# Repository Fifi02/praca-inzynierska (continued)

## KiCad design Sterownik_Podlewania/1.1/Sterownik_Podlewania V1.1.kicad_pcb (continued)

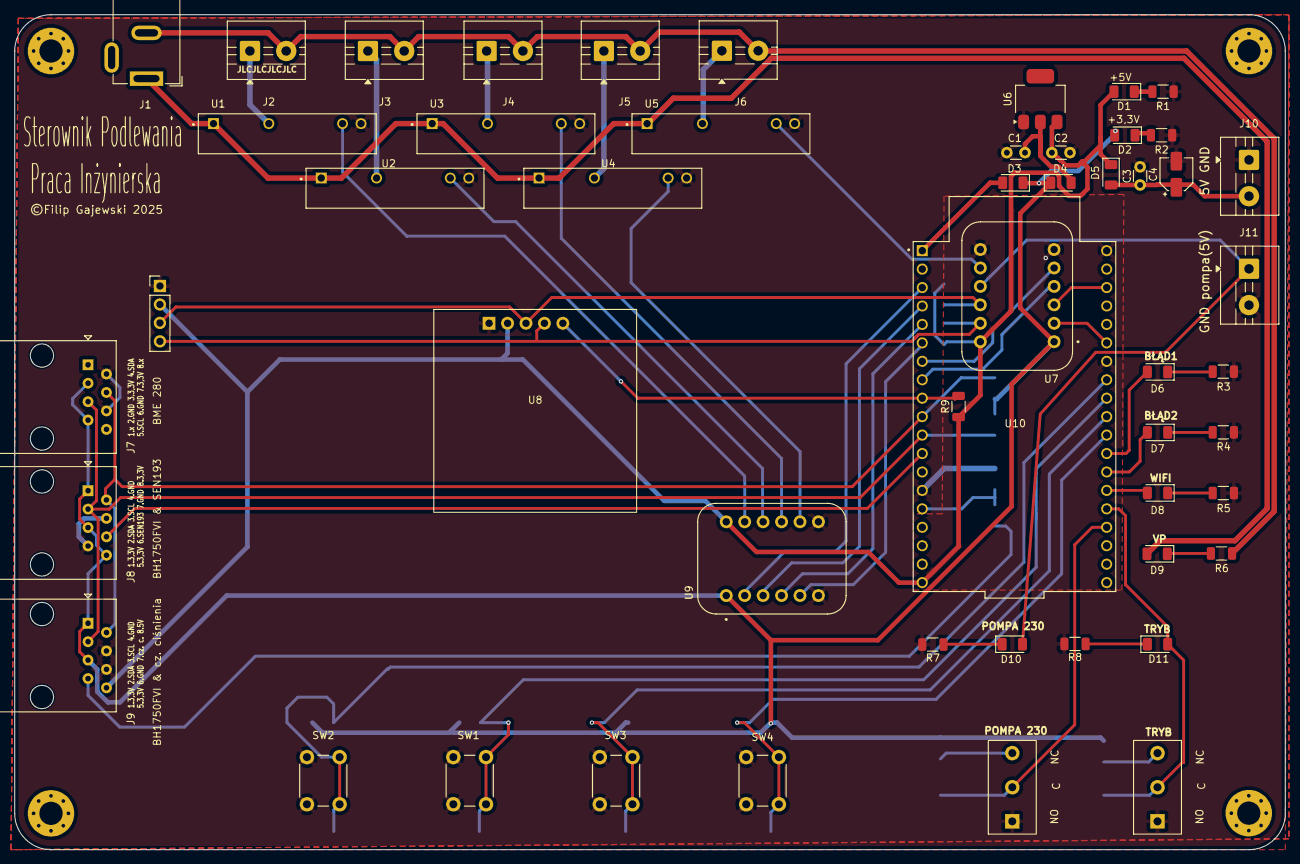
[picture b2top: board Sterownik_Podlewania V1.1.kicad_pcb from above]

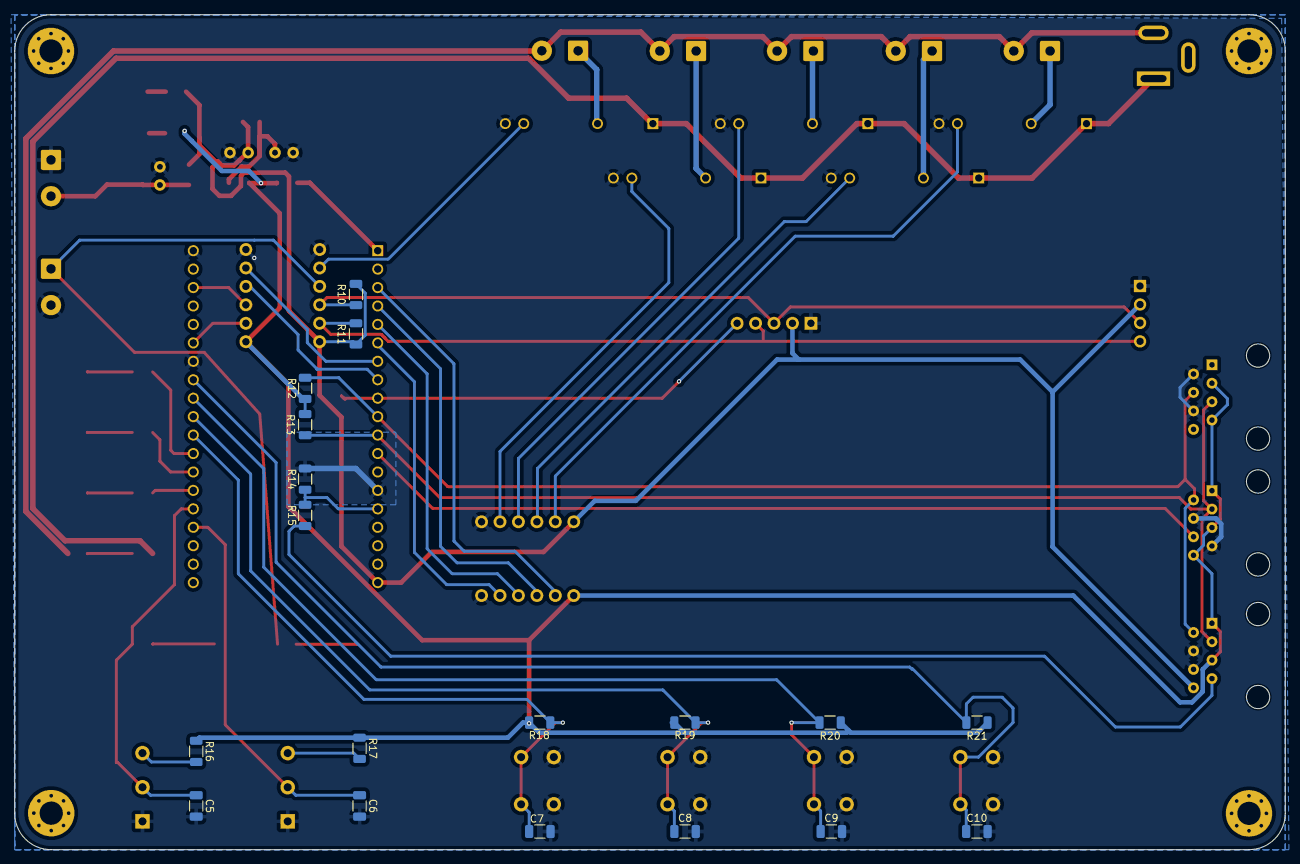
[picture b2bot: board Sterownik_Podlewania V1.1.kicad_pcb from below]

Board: 2 copper layers, 175.0 x 115.0 mm, 70 parts (18 on the bottom side), 54 nets.

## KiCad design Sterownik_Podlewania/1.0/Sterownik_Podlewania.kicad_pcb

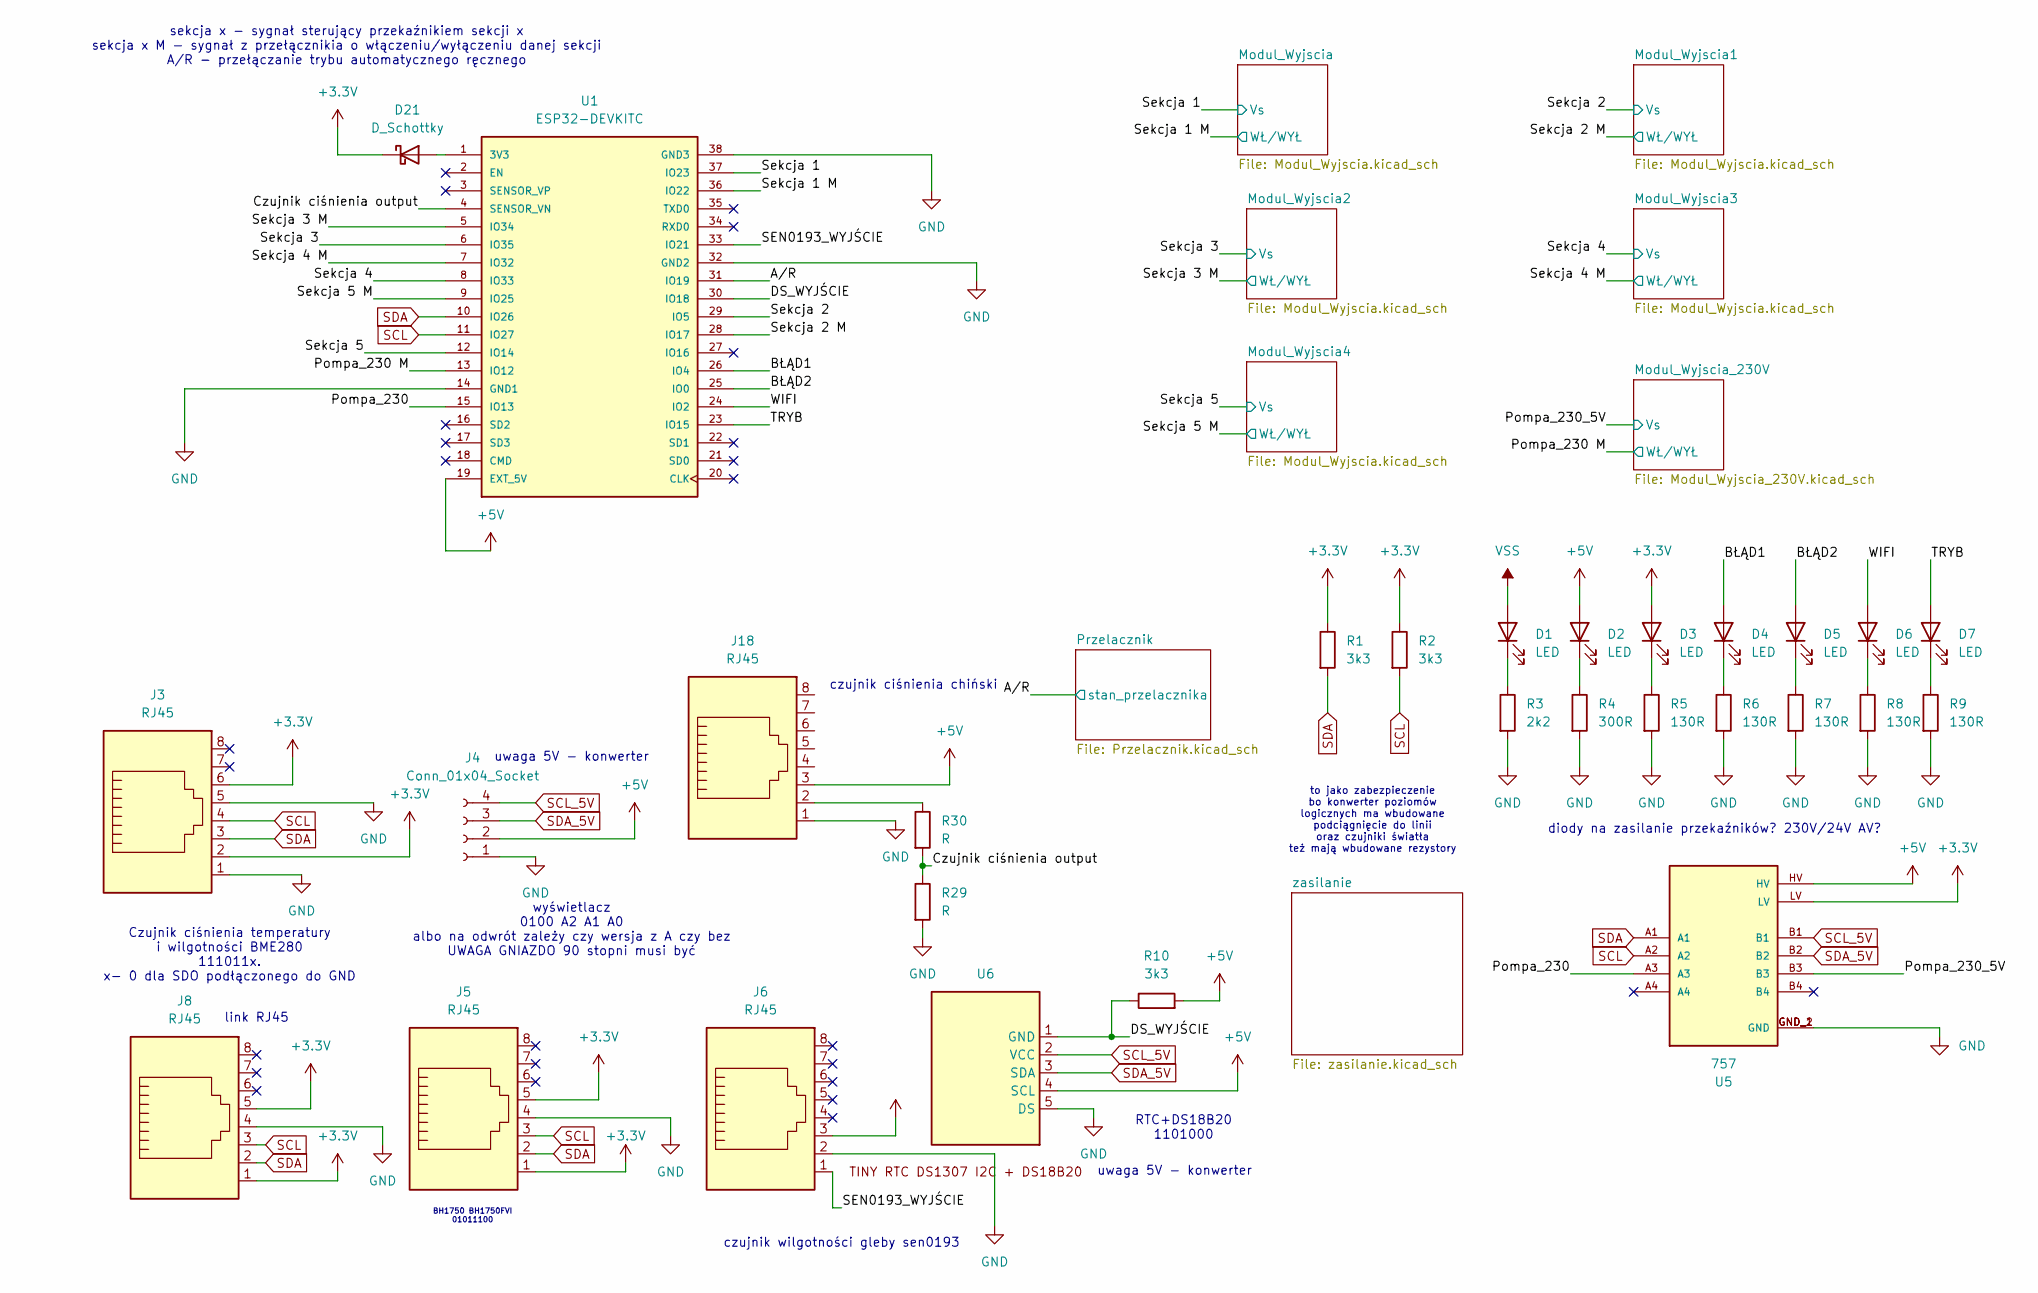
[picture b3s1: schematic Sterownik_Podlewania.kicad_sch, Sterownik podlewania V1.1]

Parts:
D1, D2, D3, D4, D5, D6, D7: LED; LED_1206_3216Metric
D21: D_Schottky; D_1206_3216Metric
J3, J5, J6, J8, J18: RJ45; RJ45_Amphenol_54602-x08_Horizontal
J4: Conn_01x04_Socket; PinHeader_1x04_P2.54mm_Vertical
R1, R2, R10: 3k3; R_1206_3216Metric
R3: 2k2; R_1206_3216Metric
R4: 300R; R_1206_3216Metric
R5, R6, R7, R8, R9: 130R; R_1206_3216Metric
R29, R30: R; R_1206_3216Metric
U1: ESP32-DEVKITC; MODULE_ESP32-DEVKITC; PARTREV N/A
U5: 757; MODULE_757; PARTREV N/A
U6: RTC DS1307 + 32kb EEPROM 24C32 I2C

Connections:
+3.3V: D3.2 (A), D21.1 (K), J3.2, J3.6, J5.1, J5.5, J6.3, J8.1, J8.5, R1.1, R2.1, U5.LV; also elsewhere on the board
+5V: D2.2 (A), J4.2, J18.3, R10.2, U1.19 (EXT_5V), U5.HV, U6.4 (SCL); also elsewhere on the board
/A/R: U1.31 (IO19); also elsewhere on the board
/BŁĄD1: D4.2 (A), U1.26 (IO4)
/BŁĄD2: D5.2 (A), U1.25 (IO0)
/Czujnik ciśnienia output: R29.1, R30.2, U1.4 (SENSOR_VN)
/DS_WYJŚCIE: R10.1, U1.30 (IO18), U6.1 (GND)
/Pompa_230: U1.15 (IO13), U5.A3
/Pompa_230 M: U1.13 (IO12); also elsewhere on the board
/Pompa_230_5V: U5.B3; also elsewhere on the board
/SEN0193_WYJŚCIE: J6.1, U1.33 (IO21)
/Sekcja 1: U1.37 (IO23); also elsewhere on the board
/Sekcja 1 M: U1.36 (IO22); also elsewhere on the board
/Sekcja 2: U1.29 (IO5); also elsewhere on the board
/Sekcja 2 M: U1.28 (IO17); also elsewhere on the board
/Sekcja 3: U1.6 (IO35); also elsewhere on the board
/Sekcja 3 M: U1.5 (IO34); also elsewhere on the board
/Sekcja 4: U1.8 (IO33); also elsewhere on the board
/Sekcja 4 M: U1.7 (IO32); also elsewhere on the board
/Sekcja 5: U1.12 (IO14); also elsewhere on the board
/Sekcja 5 M: U1.9 (IO25); also elsewhere on the board
/TRYB: D7.2 (A), U1.23 (IO15)
/WIFI: D6.2 (A), U1.24 (IO2)
GND: J3.1, J3.5, J4.1, J5.4, J6.2, J8.4, J18.1, R3.2, R4.2, R5.2, R6.2, R7.2, R8.2, R9.2, R29.2, U1.14 (GND1), U1.32 (GND2), U1.38 (GND3), U5.GND_1 (GND), U5.GND_2 (GND), U6.5 (DS); also elsewhere on the board
unnamed: D1.1 (K), R3.1
unnamed: D2.1 (K), R4.1
unnamed: D3.1 (K), R5.1
unnamed: D4.1 (K), R6.1
unnamed: D5.1 (K), R7.1
unnamed: D6.1 (K), R8.1
unnamed: D7.1 (K), R9.1
unnamed: D21.2 (A), U1.1 (3V3)
unnamed: J18.2, R30.1
SCL: J3.4, J5.3, J8.3, R2.2, U1.11 (IO27), U5.A2
SCL_5V: J4.4, U5.B1, U6.2 (VCC)
SDA: J3.3, J5.2, J8.2, R1.2, U1.10 (IO26), U5.A1
SDA_5V: J4.3, U5.B2, U6.3 (SDA)
VSS: D1.2 (A); also elsewhere on the board

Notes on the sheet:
uwaga 5V - konwerter
sekcja x - sygnał sterujący przekaźnikiem sekcji x sekcja x M - sygnał z przełącznikia o włączeniu/wyłączeniu danej sekcji A/R - przełączanie trybu automatycznego ręcznego
czujnik wilgotności gleby sen0193
diody na zasilanie przekaźników? 230V/24V AV?
to jako zabezpieczenie bo konwerter poziomów logicznych ma wbudowane podciągnięcie do linii oraz czujniki światła też mają wbudowane rezystory
BH1750 BH1750FVI 01011100
link RJ45
wyświetlacz 0100 A2 A1 A0 albo na odwrót zależy czy wersja z A czy bez UWAGA GNIAZDO 90 stopni musi być
Czujnik ciśnienia temperatury i wilgotności BME280 111011x. x- 0 dla SDO podłączonego do GND
czujnik ciśnienia chiński
RTC+DS18B20 1101000

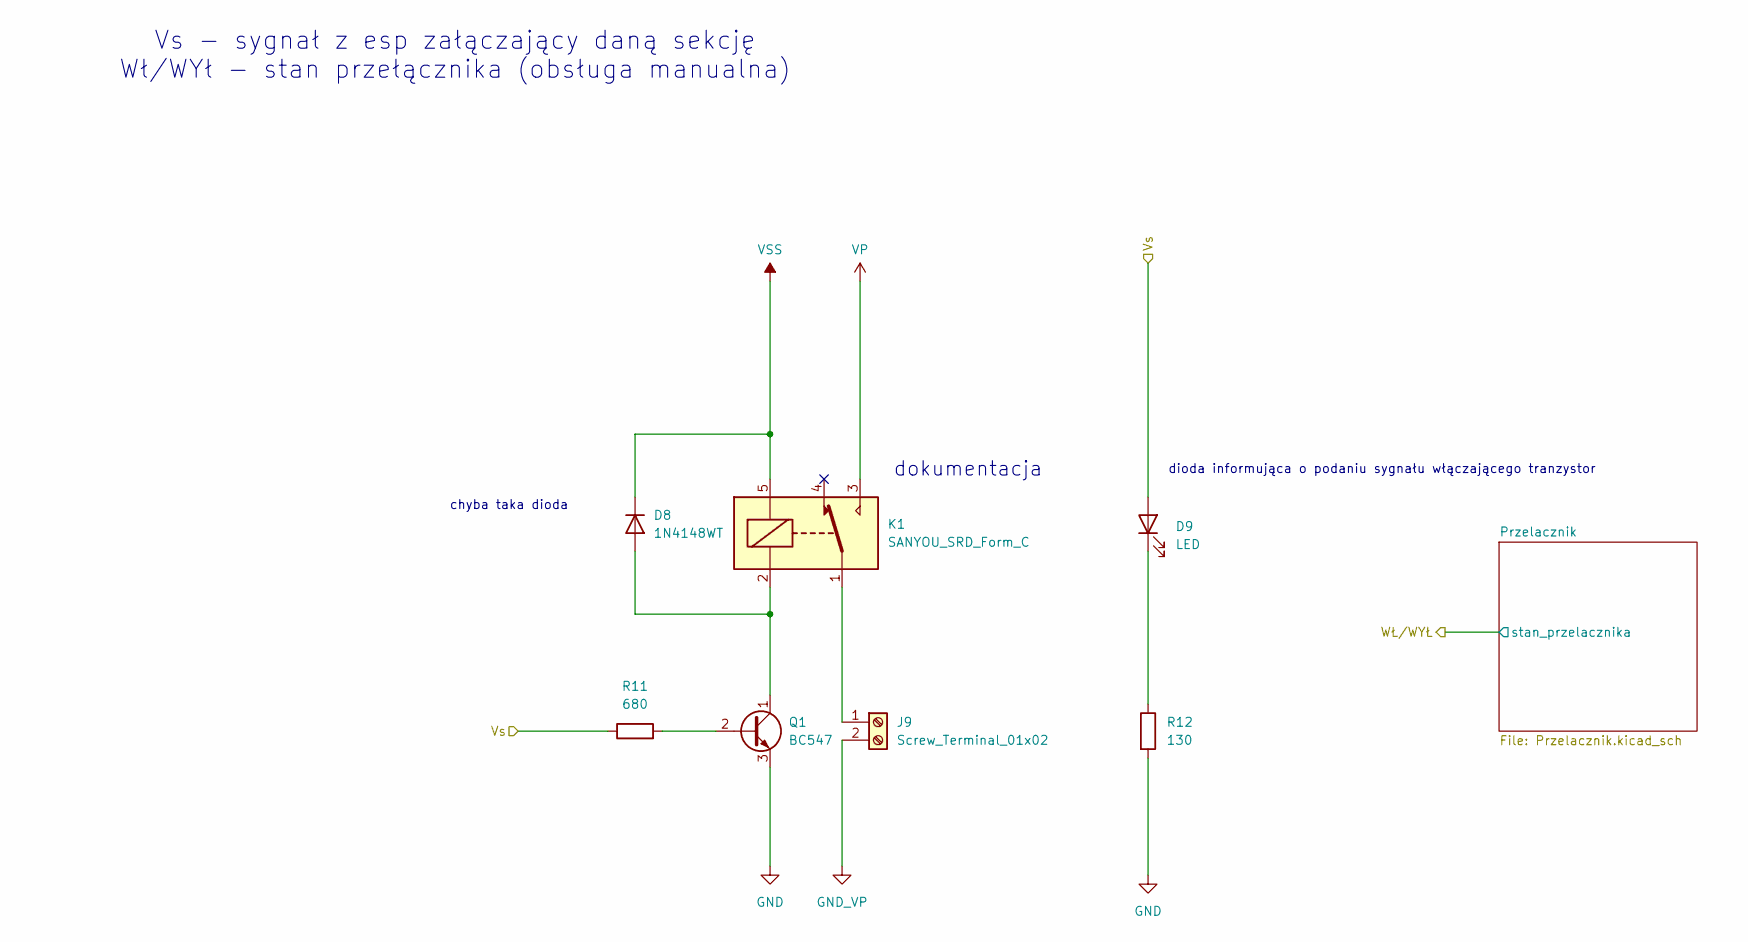
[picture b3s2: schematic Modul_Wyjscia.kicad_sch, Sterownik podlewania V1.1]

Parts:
D8: 1N4148WT; D_1206_3216Metric
D9: LED; LED_1206_3216Metric
J9: Screw_Terminal_01x02; TerminalBlock_MaiXu_MX126-5.0-02P_1x02_P5.00mm
K1: SANYOU_SRD_Form_C; Relay_SPDT_SANYOU_SRD_Series_Form_C
Q1: BC547; TO-92_Inline
R11: 680; R_1206_3216Metric
R12: 130; R_1206_3216Metric

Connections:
/Sekcja 1: D9.2 (A), R11.1; also elsewhere on the board
GND: Q1.3 (E), R12.2; also elsewhere on the board
GND_VP: J9.2; also elsewhere on the board
unnamed: D8.2 (A), K1.2, Q1.1 (C)
unnamed: D9.1 (K), R12.1
unnamed: J9.1, K1.1
unnamed: Q1.2 (B), R11.2
VP: K1.3; also elsewhere on the board
VSS: D8.1 (K), K1.5; also elsewhere on the board

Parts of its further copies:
D10, D12, D14, D16: 1N4148WT; D_1206_3216Metric
D11, D13, D15, D17: LED; LED_1206_3216Metric
J10, J11, J12, J13: Screw_Terminal_01x02; TerminalBlock_MaiXu_MX126-5.0-02P_1x02_P5.00mm
K2, K3, K4, K5: SANYOU_SRD_Form_C; Relay_SPDT_SANYOU_SRD_Series_Form_C
Q2, Q3, Q4, Q5: BC547; TO-92_Inline
R13, R15, R17, R19: 680; R_1206_3216Metric
R14, R16, R18, R20: 130; R_1206_3216Metric

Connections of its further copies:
/Sekcja 2: D11.2 (A), R13.1; also elsewhere on the board
/Sekcja 3: D13.2 (A), R15.1; also elsewhere on the board
/Sekcja 4: D15.2 (A), R17.1; also elsewhere on the board
/Sekcja 5: D17.2 (A), R19.1; also elsewhere on the board
GND: Q2.3 (E), Q3.3 (E), Q4.3 (E), Q5.3 (E), R14.2, R16.2, R18.2, R20.2; also elsewhere on the board
GND_VP: J10.2, J11.2, J12.2, J13.2; also elsewhere on the board
unnamed: D10.2 (A), K2.2, Q2.1 (C)
unnamed: D11.1 (K), R14.1
unnamed: D12.2 (A), K3.2, Q3.1 (C)
unnamed: D13.1 (K), R16.1
unnamed: D14.2 (A), K4.2, Q4.1 (C)
unnamed: D15.1 (K), R18.1
unnamed: D16.2 (A), K5.2, Q5.1 (C)
unnamed: D17.1 (K), R20.1
unnamed: J10.1, K2.1
unnamed: J11.1, K3.1
unnamed: J12.1, K4.1
unnamed: J13.1, K5.1
unnamed: Q2.2 (B), R13.2
unnamed: Q3.2 (B), R15.2
unnamed: Q4.2 (B), R17.2
unnamed: Q5.2 (B), R19.2
VP: K2.3, K3.3, K4.3, K5.3; also elsewhere on the board
VSS: D10.1 (K), D12.1 (K), D14.1 (K), D16.1 (K), K2.5, K3.5, K4.5, K5.5; also elsewhere on the board

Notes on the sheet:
Vs - sygnał z esp załączający daną sekcję Wł/WYł - stan przełącznika (obsługa manualna)
dioda informująca o podaniu sygnału włączającego tranzystor
chyba taka dioda
dokumentacja

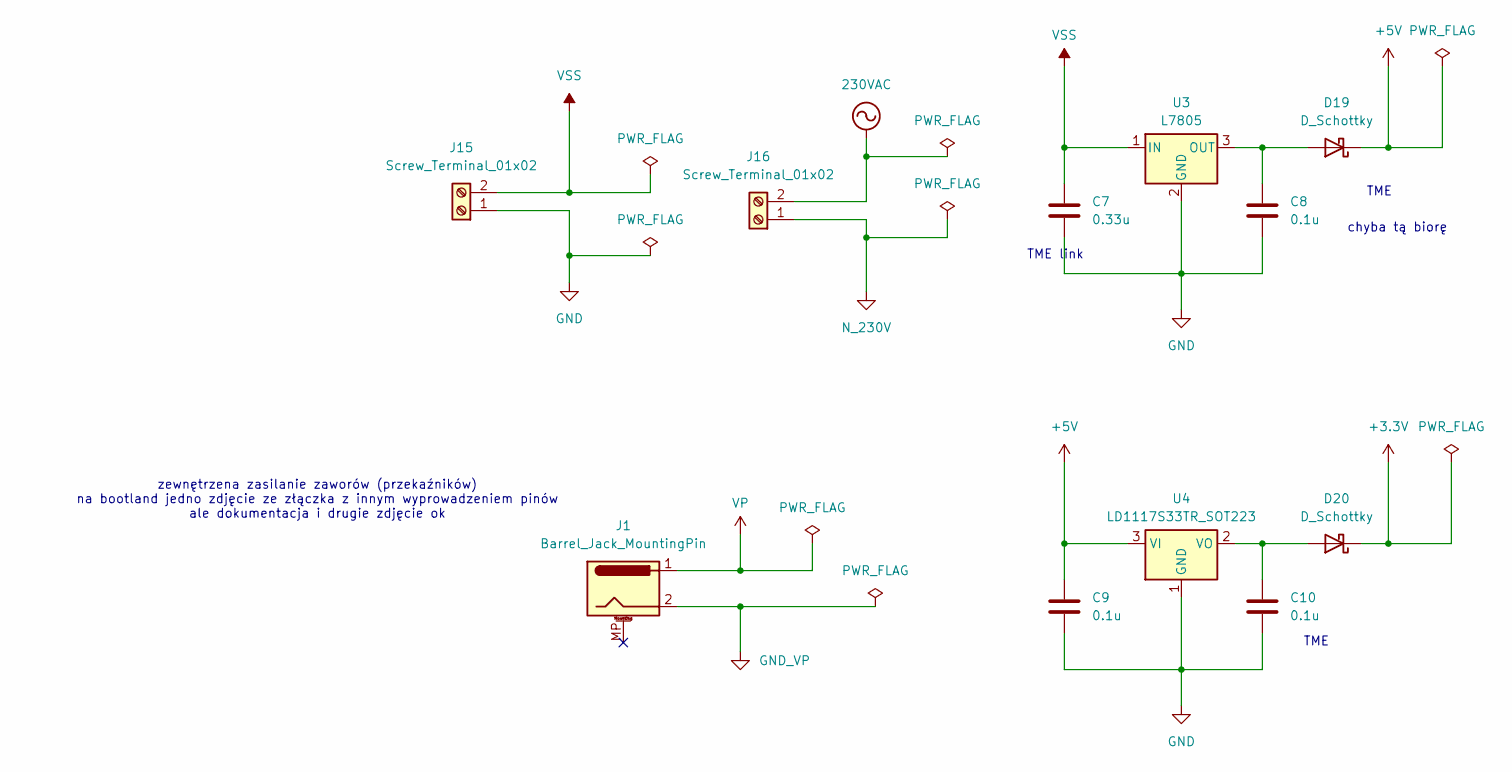
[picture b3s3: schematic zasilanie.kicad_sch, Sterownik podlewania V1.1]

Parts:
C7: 0.33u; CP_Elec_4x5.4
C8, C9, C10: 0.1u; C_Disc_D3.0mm_W1.6mm_P2.50mm
D19, D20: D_Schottky; D_1206_3216Metric
J1: Barrel_Jack_MountingPin; BarrelJack_GCT_DCJ200-10-A_Horizontal
J15, J16: Screw_Terminal_01x02; TerminalBlock_MaiXu_MX126-5.0-02P_1x02_P5.00mm
U3: L7805; TO-220-3_Vertical
U4: LD1117S33TR_SOT223; SOT-223

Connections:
230VAC: J16.2; also elsewhere on the board
+3.3V: D20.1 (K); also elsewhere on the board
+5V: C9.1, D19.1 (K), U4.3 (VI); also elsewhere on the board
GND: C7.2, C8.2, C9.2, C10.2, J15.1, U3.2 (GND), U4.1 (GND); also elsewhere on the board
GND_VP: J1.2; also elsewhere on the board
N_230V: J16.1; also elsewhere on the board
unnamed: C8.1, D19.2 (A), U3.3 (OUT)
unnamed: C10.1, D20.2 (A), U4.2 (VO)
VP: J1.1; also elsewhere on the board
VSS: C7.1, J15.2, U3.1 (IN); also elsewhere on the board

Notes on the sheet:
TME link
TME
chyba tą biorę
zewnętrzena zasilanie zaworów (przekaźników) na bootland jedno zdjęcie ze złączka z innym wyprowadzeniem pinów ale dokumentacja i drugie zdjęcie ok

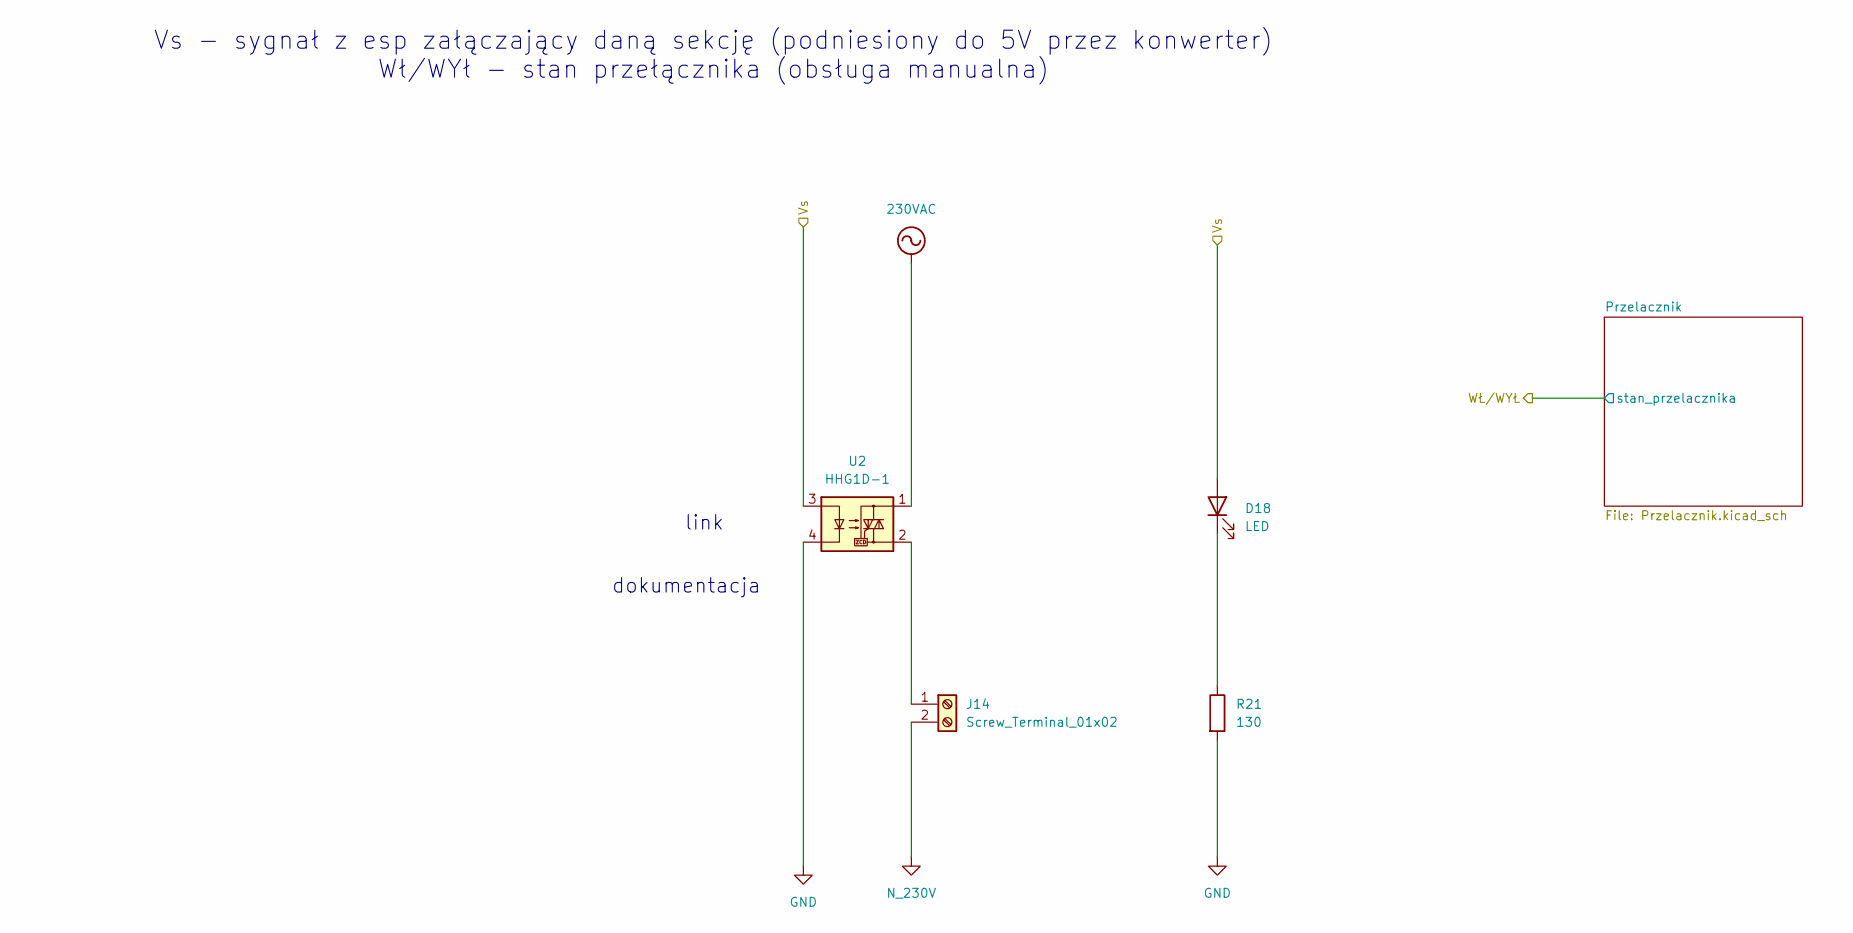
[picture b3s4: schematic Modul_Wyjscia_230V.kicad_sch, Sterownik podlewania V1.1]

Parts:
D18: LED; LED_1206_3216Metric
J14: Screw_Terminal_01x02; TerminalBlock_MaiXu_MX126-5.0-02P_1x02_P5.00mm
R21: 130; R_1206_3216Metric
U2: HHG1D-1; RELAY_G3MB-202P

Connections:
230VAC: U2.1; also elsewhere on the board
/Pompa_230_5V: D18.2 (A), U2.3; also elsewhere on the board
GND: R21.2, U2.4; also elsewhere on the board
N_230V: J14.2; also elsewhere on the board
unnamed: D18.1 (K), R21.1
unnamed: J14.1, U2.2

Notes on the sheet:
Vs - sygnał z esp załączający daną sekcję (podniesiony do 5V przez konwerter) Wł/WYł - stan przełącznika (obsługa manualna)
dokumentacja
link

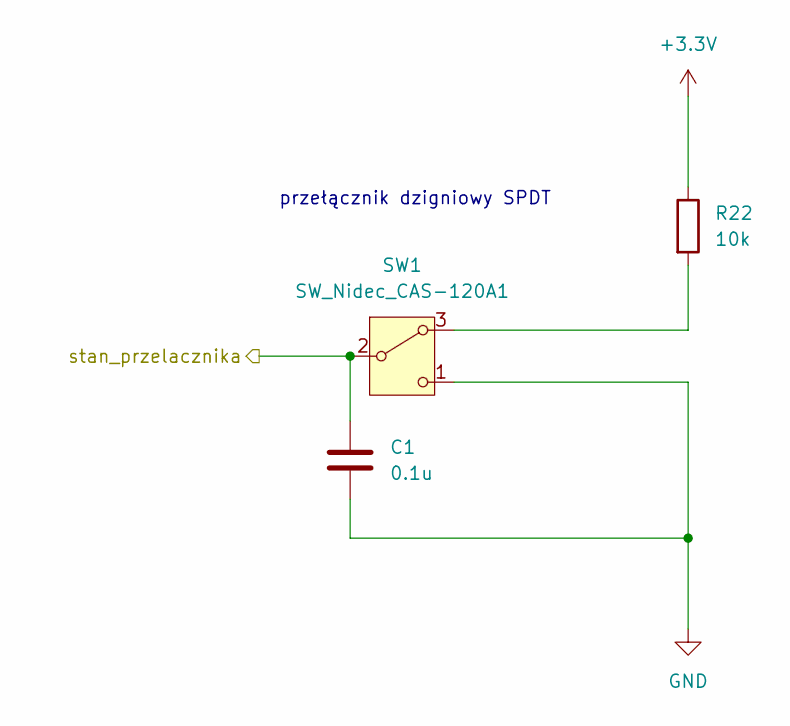
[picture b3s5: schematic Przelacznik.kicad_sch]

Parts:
C1: 0.1u; C_1206_3216Metric
R22: 10k; R_1206_3216Metric
SW1: SW_Nidec_CAS-120A1; Toggle Switch Bootland 4.7mm

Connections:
+3.3V: R22.1; also elsewhere on the board
/A/R: C1.1, SW1.2 (B); also elsewhere on the board
GND: C1.2, SW1.1 (C); also elsewhere on the board
unnamed: R22.2, SW1.3 (A)

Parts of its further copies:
C2, C3, C4, C5, C6, C11: 0.1u; C_1206_3216Metric
R23, R24, R25, R26, R27, R28: 10k; R_1206_3216Metric
SW2, SW3, SW4, SW5, SW6, SW8: SW_Nidec_CAS-120A1; Toggle Switch Bootland 4.7mm

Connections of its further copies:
+3.3V: R23.1, R24.1, R25.1, R26.1, R27.1, R28.1; also elsewhere on the board
/Pompa_230 M: C11.1, SW8.2 (B); also elsewhere on the board
/Sekcja 1 M: C2.1, SW2.2 (B); also elsewhere on the board
/Sekcja 2 M: C3.1, SW3.2 (B); also elsewhere on the board
/Sekcja 3 M: C4.1, SW4.2 (B); also elsewhere on the board
/Sekcja 4 M: C5.1, SW5.2 (B); also elsewhere on the board
/Sekcja 5 M: C6.1, SW6.2 (B); also elsewhere on the board
GND: C2.2, C3.2, C4.2, C5.2, C6.2, C11.2, SW2.1 (C), SW3.1 (C), SW4.1 (C), SW5.1 (C), SW6.1 (C), SW8.1 (C); also elsewhere on the board
unnamed: R23.2, SW2.3 (A)
unnamed: R24.2, SW3.3 (A)
unnamed: R25.2, SW4.3 (A)
unnamed: R26.2, SW5.3 (A)
unnamed: R27.2, SW6.3 (A)
unnamed: R28.2, SW8.3 (A)

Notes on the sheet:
przełącznik dzigniowy SPDT

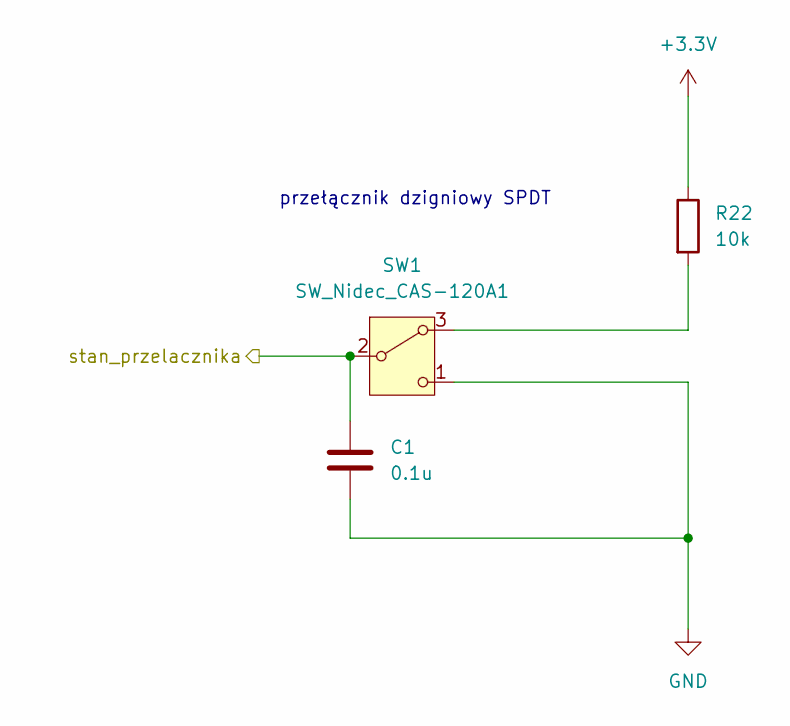
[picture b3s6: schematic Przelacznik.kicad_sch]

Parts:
C1: 0.1u; C_1206_3216Metric
R22: 10k; R_1206_3216Metric
SW1: SW_Nidec_CAS-120A1; Nidec_Copal_CAS-120A

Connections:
+3.3V: R22.1; also elsewhere on the board
/A/R: C1.1, SW1.2 (B); also elsewhere on the board
GND: C1.2, SW1.1 (C); also elsewhere on the board
unnamed: R22.2, SW1.3 (A)

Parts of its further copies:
C2, C3, C4, C5, C6, C11: 0.1u; C_1206_3216Metric
R23, R24, R25, R26, R27, R28: 10k; R_1206_3216Metric
SW2, SW3, SW4, SW5, SW6, SW8: SW_Nidec_CAS-120A1; Nidec_Copal_CAS-120A

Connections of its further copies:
+3.3V: R23.1, R24.1, R25.1, R26.1, R27.1, R28.1; also elsewhere on the board
/Pompa_230 M: C11.1, SW8.2 (B); also elsewhere on the board
/Sekcja 1 M: C2.1, SW2.2 (B); also elsewhere on the board
/Sekcja 2 M: C3.1, SW3.2 (B); also elsewhere on the board
/Sekcja 3 M: C4.1, SW4.2 (B); also elsewhere on the board
/Sekcja 4 M: C5.1, SW5.2 (B); also elsewhere on the board
/Sekcja 5 M: C6.1, SW6.2 (B); also elsewhere on the board
GND: C2.2, C3.2, C4.2, C5.2, C6.2, C11.2, SW2.1 (C), SW3.1 (C), SW4.1 (C), SW5.1 (C), SW6.1 (C), SW8.1 (C); also elsewhere on the board
unnamed: R23.2, SW2.3 (A)
unnamed: R24.2, SW3.3 (A)
unnamed: R25.2, SW4.3 (A)
unnamed: R26.2, SW5.3 (A)
unnamed: R27.2, SW6.3 (A)
unnamed: R28.2, SW8.3 (A)

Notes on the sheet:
przełącznik dzigniowy SPDT

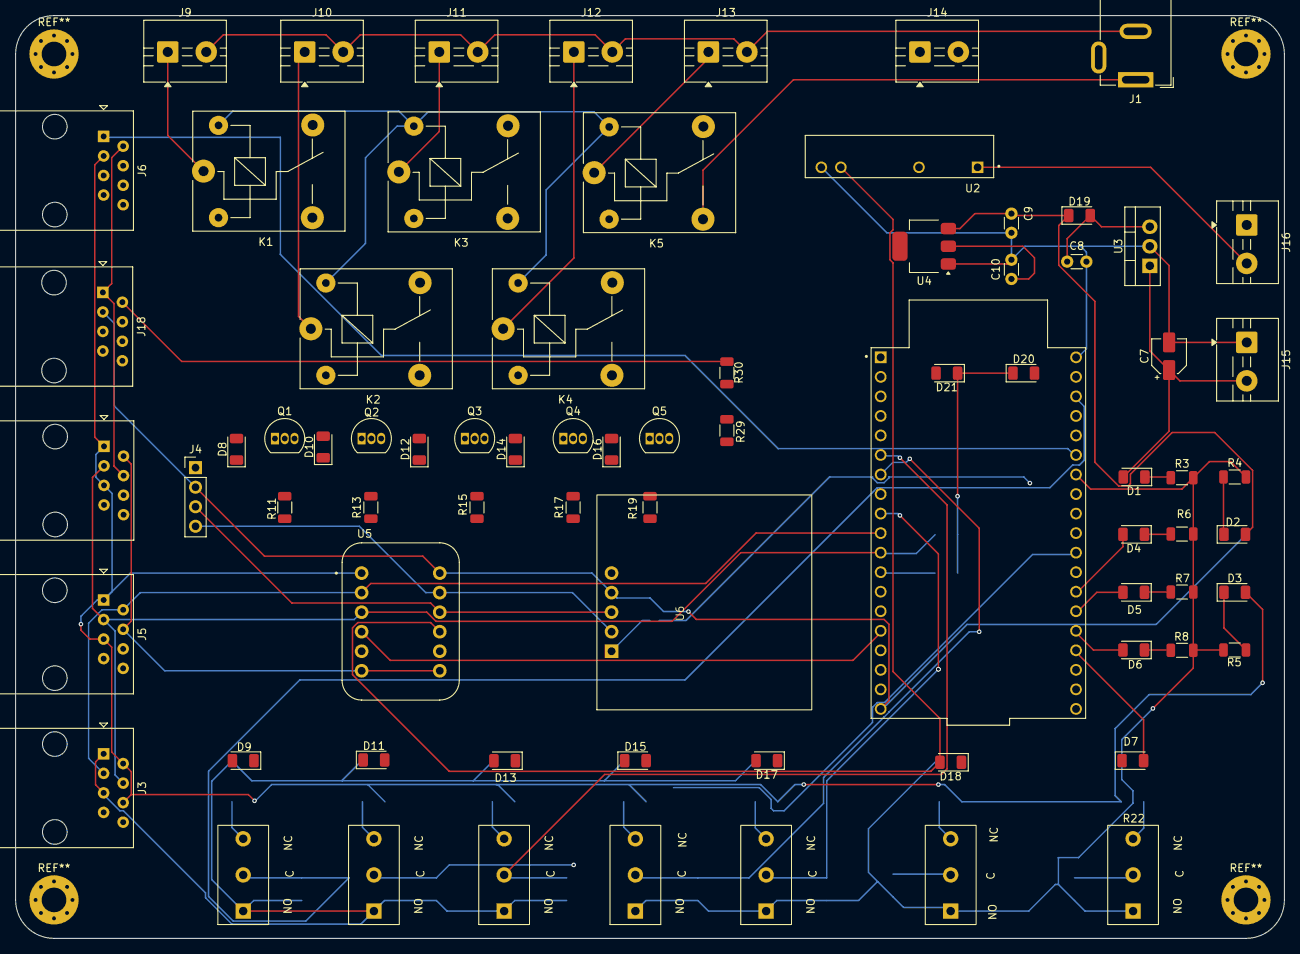
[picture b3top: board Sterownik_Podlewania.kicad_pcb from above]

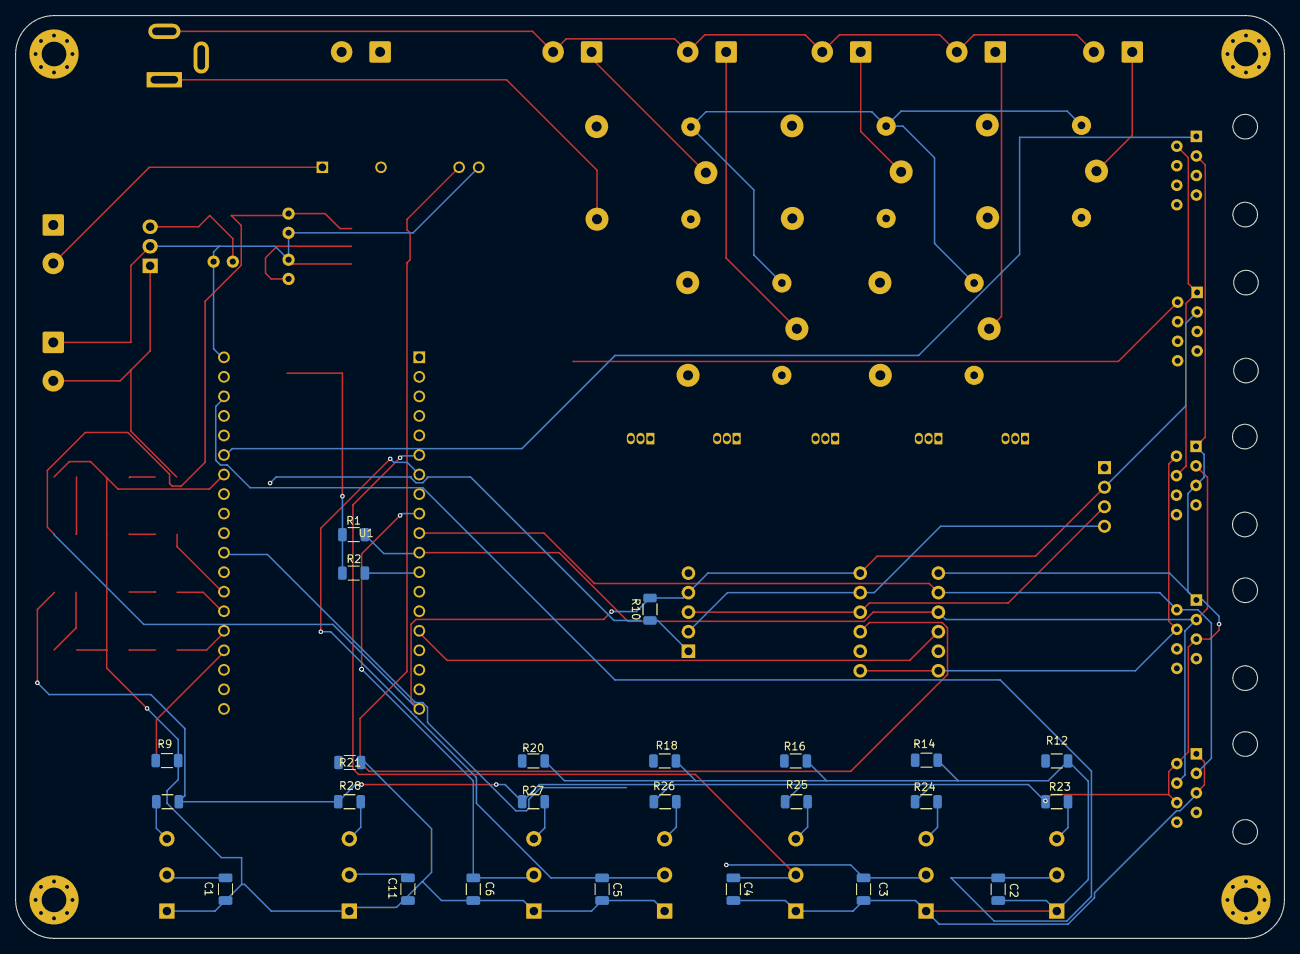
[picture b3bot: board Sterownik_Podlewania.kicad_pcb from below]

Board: 2 copper layers, 165.0 x 120.0 mm, 100 parts (24 on the bottom side), 73 nets.

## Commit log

2025-09-17 Pierwsze koty za płoty
2025-09-18 Dodanie zasilania, sekcji czujników światła, modyfikacja przełączników, dodanie znaczników
2025-10-04 Modyfikacja sekcji czujników
2025-10-04 Dodanie adresów I2C, linków, czujnika temp, konwerter poziomów napięć
2025-10-05 Dodanie większośi footprinów, dodanie osobno sekcji na 230V, dodanie jacka DC
2025-10-07 Dodanie dokumentacji przełączników, sprawdzenie konwertera I2C, dodanie sekcji przełącznika, dodanie DIP swticha do przełączania zasialania zew, wydzielenie sekcji zasilania
2025-10-08 Poprawki estetyczne schematu
2025-10-09 Dodanie gniazd ethernet, poprawienie większośc ERC
2025-10-09 Wstępny układ PCB
2025-10-10 Dodanie footprintów schotky, kondesatorów
2025-10-12 Dodanie modeli 3d, nowy footprint do przełącznika, przerzucenie na drugą stronę płytki elementów, wstępne rozdzielenie elemntów pasywnych
2025-10-14 dodanie modeli 3d, poprawa footprintu RTC
2025-10-15 Wstępny finalny rozkład płytki, narysowanie outlinu
2025-10-16 Zmiana footprintó diód przekaźnika na schottky,finalne ułożenie przekaźników, diód itp
2025-10-18 Wersja 1.1 rozkład footprintów, dopracowanie schematu V1.1
2025-10-18 Pociągnięcie prawie wszystkich ścieżek, dodanie rezystorów do I2C 5V
2025-10-19 Poprawiono błędy połączeń SDA,SCL, dodno drugą magistralę I2C, pociągnięcie nowych ścieżek
2025-10-23 Dodanie modułu zasilania, wstępny schemat
2025-10-24 Poprawki schematu modułu zaworu, usunięcie przekaźnika, przygotowanie schematu zasilania
2025-10-24 Usunięcie zewnętrzego zasilania 12 i stabilizatora napięcia, korekcja zasilania wzmacniacz operacyjny moduł zasilania
2025-10-25 Poprawki moduł zasilania, stowrzenie płytki, zostało trochę błędów, zapomniałem dać mouting holes
2025-10-26 Gotowy do zatwierdzenia moduł zasilaina
2025-10-26 Werja plików podesłana Mariuszkowi, dodane opisy i numeracja poprawna dla steronwika, w module poprawniono opis złącze ethernet
2025-10-27 Testing MQTT + apllikacja webowa+ baza danych. Dodanie zworek pozwalaąjcych na zaminę trybu przetwornicy mppt, zmiana układu zasilania zgodnie z zaleceniami Pana Mariusza.
2025-11-20 Kod websocket, kod stonka demo, kod sterownika - wszystkie taski poza bt wstepnie ogarniete
